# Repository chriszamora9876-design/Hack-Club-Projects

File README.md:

# Hack-Club-Projects
projects for hack club

Wanted to see how hard it was to actually design a pcb and turn it into a functioning project (turns out it was hard to learn).
I decided to stray away from the design by routing the PCB in a unconventional but unique way, along with defiantly doing a different case design.
I aimed for a NYC theme on top of the case first because I love the city, and second because I love modeling skylines (even on Desmos).
I struggled a little but in the beginning since it was my first time using Fusion and KiCAD for actually real-life projects and I was afraid to mess up.
Eventually, I go the hang of it and I defiantly hope to continue improving my skills through making more projects through Hack Club!!!

Here is a BOM of all the materials you would need to build this!

| Quantity | Part Name | Part Price |
| :--- | :--- | :--- |
| 1x | Seeed XIAO ESP32C3 | $4.99 |
| 12x | MX-Style Keyboard Switches | $4.50 |
| 12x | White Blank DSA Keycaps | $4.00 |
| 12x | Through-Hole 1N4148 Diodes | $3.49 |
| 1x | 2.25in TFT Screen | $10.34 |
| 1x | 3.3V Piezo Buzzer | $2.27 |
| 1x | 2.54mm 8 Pin Male Header | $1.50 |
| 8x | 20cm Female-Female Jumper Wires | $4.00 |
| 8x | M3x5x4 Heatset Inserts | $8.62 |
| 4x | M3x8mm Screws | $9.68 |
| 4x | M3x16mm Screws | $6.20 |

Total Cost Prediciton:
~$45 USD

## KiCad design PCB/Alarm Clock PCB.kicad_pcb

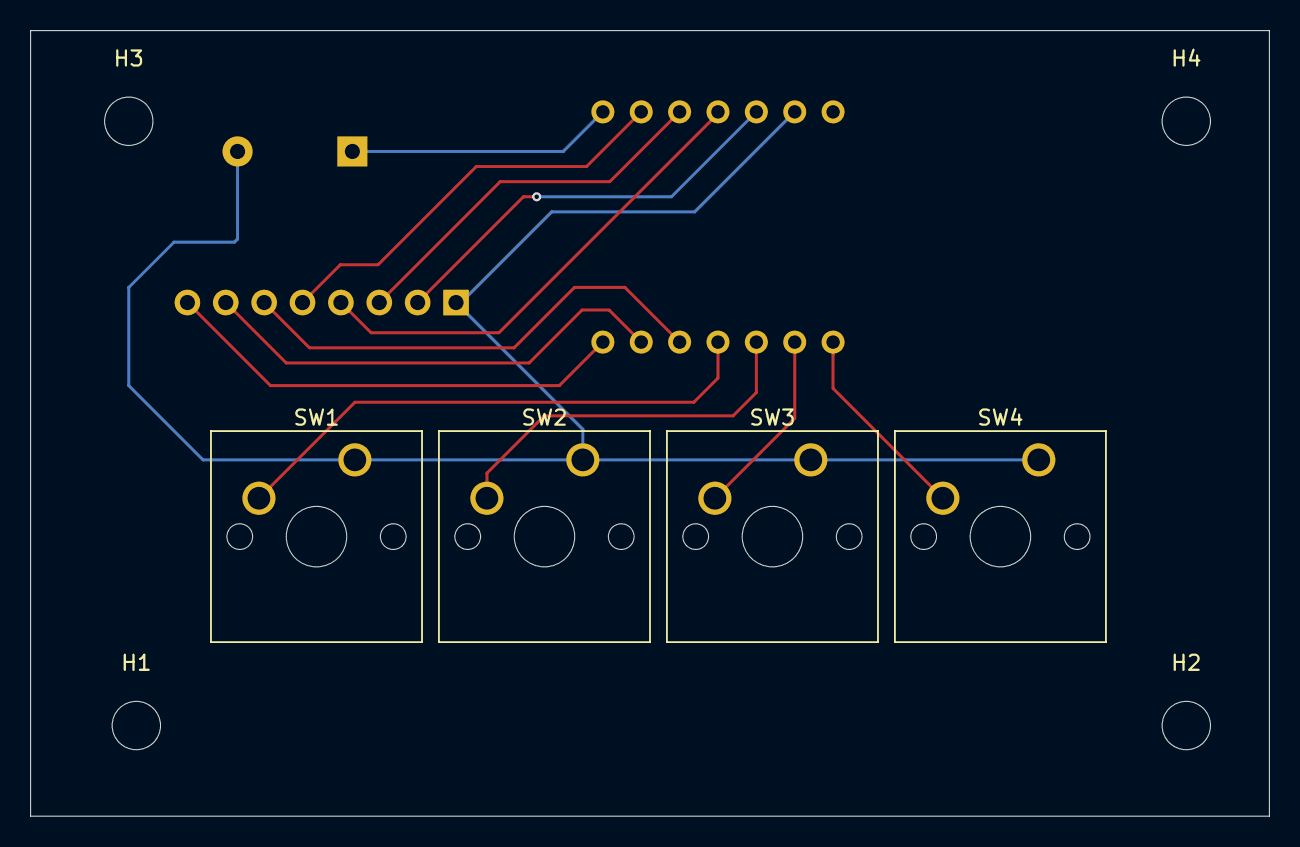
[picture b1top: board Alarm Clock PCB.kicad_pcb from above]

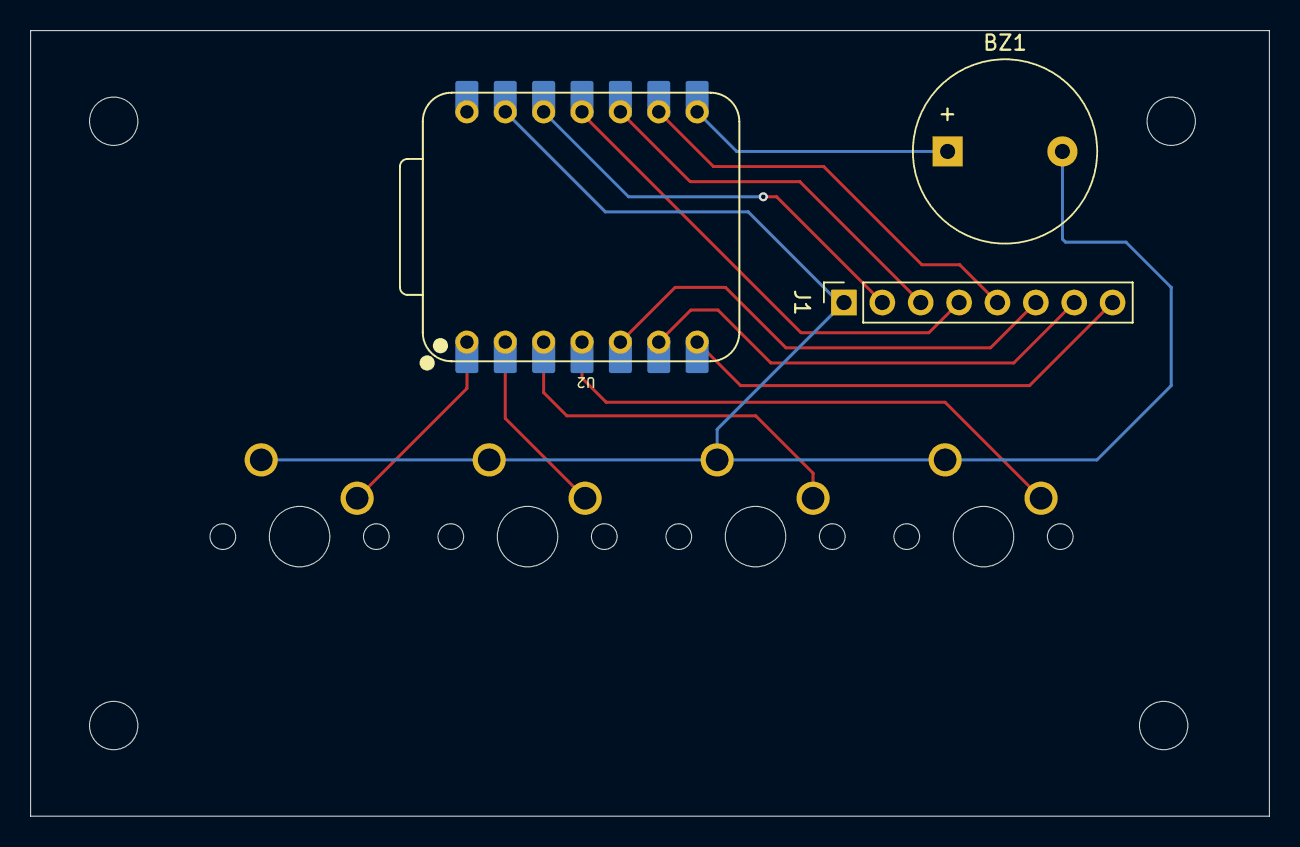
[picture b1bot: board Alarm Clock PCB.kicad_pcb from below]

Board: 2 copper layers, 82.0 x 52.0 mm, 11 parts (3 on the bottom side), 13 nets.

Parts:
BZ1: Buzzer; Buzzer_12x9.5RM7.6
H1, H2, H3, H4: MountingHole; MountingHole_3.2mm_M3
J1: Conn_01x08_Pin; PinSocket_1x08_P2.54mm_Vertical
SW1, SW2, SW3, SW4: SW_Push; SW_Cherry_MX_1.00u_PCB
U2: XIAO-ESP32-C3-SMD; XIAO-ESP32-C3-DIP

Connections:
+3.3V: J1.2, U2.12 (3V3_OUT)
/BL: J1.8, U2.7 (D6)
/CS: J1.7, U2.6 (D5)
/DC: J1.6, U2.5 (D4)
/RST: J1.5, U2.9 (D8)
/SCL: J1.3, U2.10 (D9/BOOT)
/SDA: J1.4, U2.11 (D10)
GND: BZ1.2 (-), J1.1, SW1.1, SW2.1, SW3.1, SW4.1, U2.13 (GND)
unnamed: BZ1.1 (+), U2.8 (D7)
unnamed: SW4.2, U2.1 (D0)
unnamed: SW3.2, U2.2 (D1)
unnamed: SW2.2, U2.3 (D2)
unnamed: SW1.2, U2.4 (D3)
